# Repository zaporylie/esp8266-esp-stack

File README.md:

# ESP stack

## Goal

Cheap and easy to use (and make it at home) development kit for ESP8266 based projects.

## Available boards

* core, compatible with esp-07 esp-12 and esp-12e
* pl2303 - use it together with external FTDI board

## Contribution

## Licence

This project is licenced under GNU General Public Licence, version 2 or later. You can take it from here, use in free or commercial projects. However, you must distribute it under the GPL version 2 or later, so those you sell it to must be allowed to modify and redistribute it as well.

## Credits

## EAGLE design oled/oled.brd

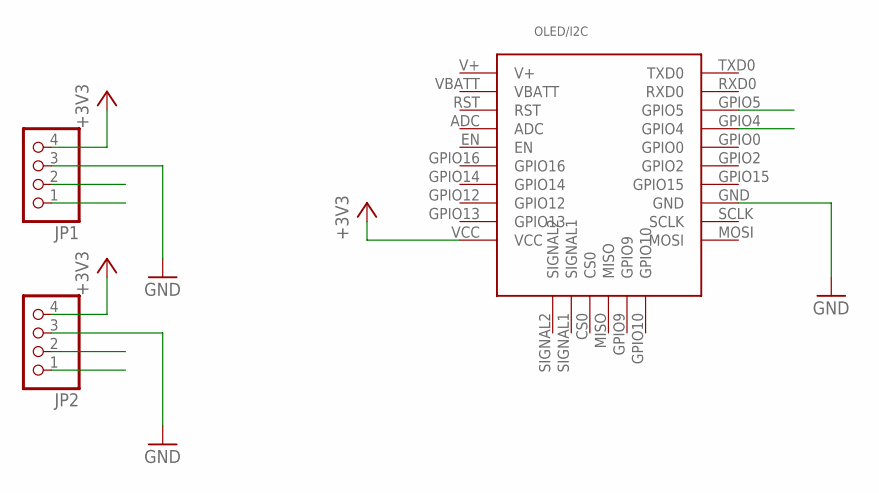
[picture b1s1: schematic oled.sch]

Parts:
JP1, JP2: PINHD-1X4; 1X04
OLED/I2C: ESP-BOARD

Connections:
+3V3: JP1.4, JP2.4, OLED/I2C.VCC
GND: JP1.3, JP2.3, OLED/I2C.GND
SCL: JP1.2, JP2.2, OLED/I2C.GPIO5
SDA: JP1.1, JP2.1, OLED/I2C.GPIO4
V+: OLED/I2C.V+
VBATT: OLED/I2C.VBATT

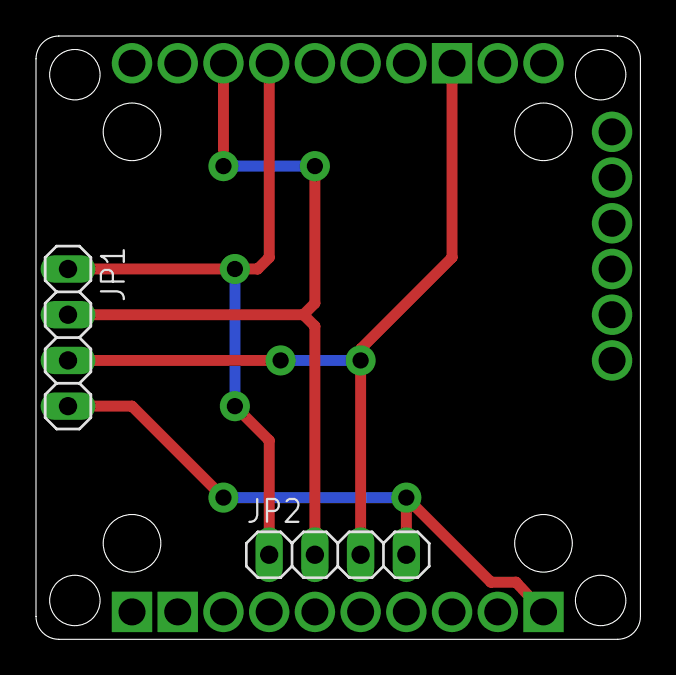
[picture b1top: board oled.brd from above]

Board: 2 copper layers, 33.6 x 33.5 mm, 3 parts (0 on the bottom side), 4 nets.

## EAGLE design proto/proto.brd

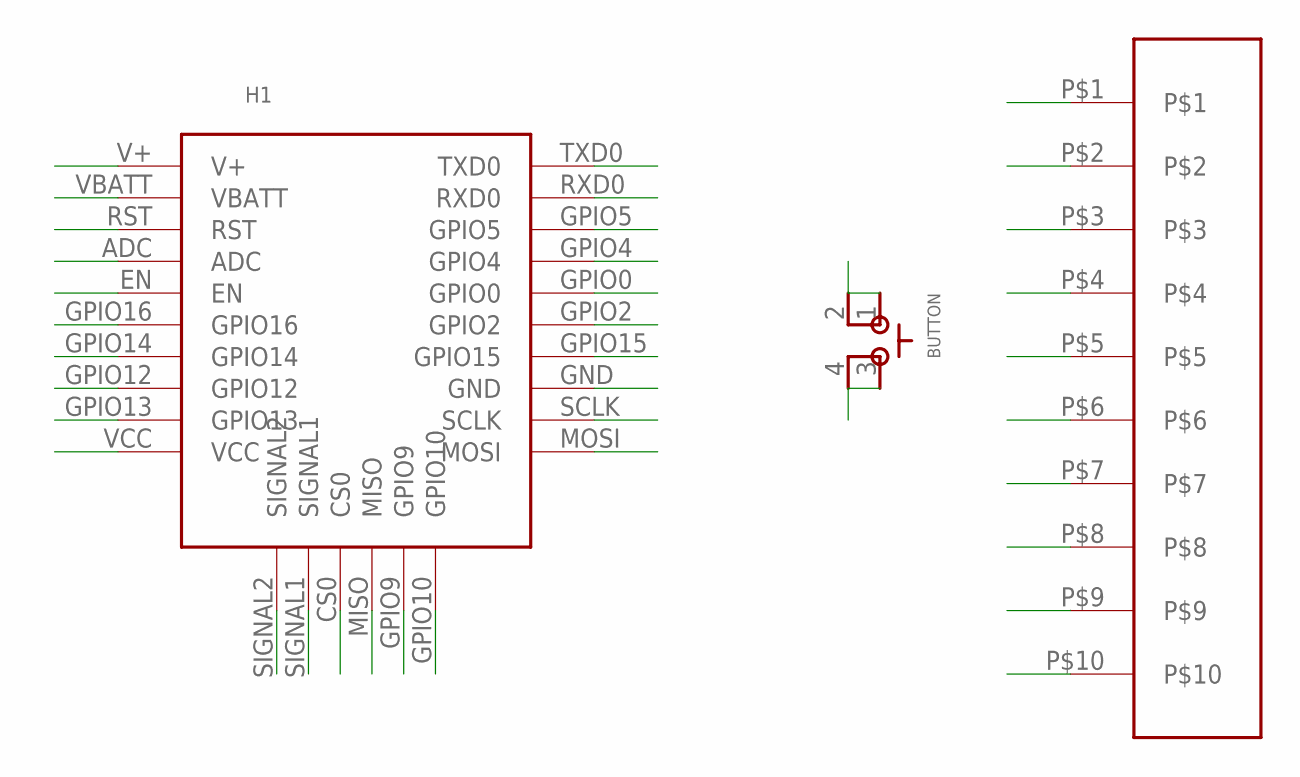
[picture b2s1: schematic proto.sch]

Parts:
BUTTON: SKSCLDE010
H1: ESP-BOARD
U$1: 1X10-EDGE

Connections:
ADC: H1.ADC
CS0: H1.CS0
EN: H1.EN
GND: H1.GND
GPIO0: H1.GPIO0
GPIO2: H1.GPIO2
GPIO4: H1.GPIO4
GPIO5: H1.GPIO5
GPIO9: H1.GPIO9
GPIO10: H1.GPIO10
GPIO12: H1.GPIO12
GPIO13: H1.GPIO13
GPIO14: H1.GPIO14
GPIO15: H1.GPIO15
GPIO16: H1.GPIO16
MISO: H1.MISO
MOSI: H1.MOSI
P0: U$1.P$10
P1: U$1.P$9
P2: U$1.P$8
P3: U$1.P$7
P4: U$1.P$6
P5: U$1.P$5
P6: U$1.P$4
P7: U$1.P$3
P8: U$1.P$2
P9: U$1.P$1
RST: H1.RST
RXD0: H1.RXD0
SCLK: H1.SCLK
SIGNAL1: H1.SIGNAL1
SIGNAL2: H1.SIGNAL2
SW1: BUTTON.3 (4), BUTTON.4 (3)
SW2: BUTTON.1, BUTTON.2
TXD0: H1.TXD0
V+: H1.V+
VBATT: H1.VBATT
VCC: H1.VCC

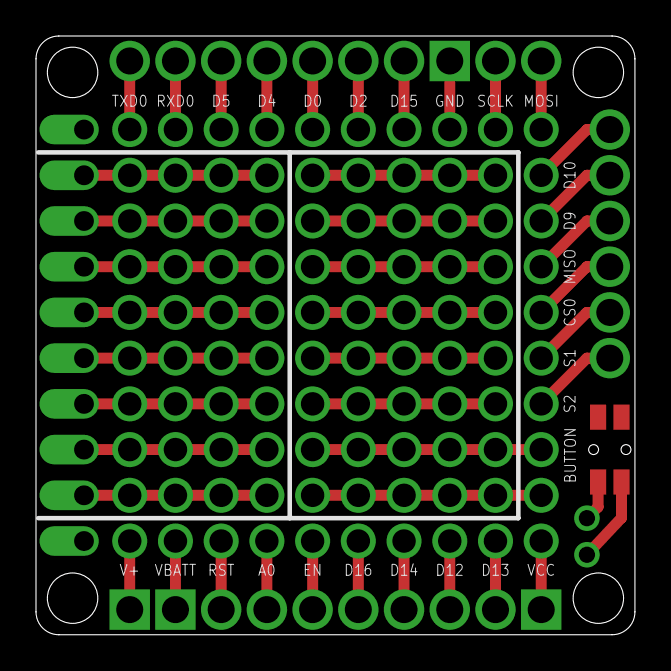
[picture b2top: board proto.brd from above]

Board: 2 copper layers, 33.3 x 33.3 mm, 3 parts (0 on the bottom side), 2 nets.

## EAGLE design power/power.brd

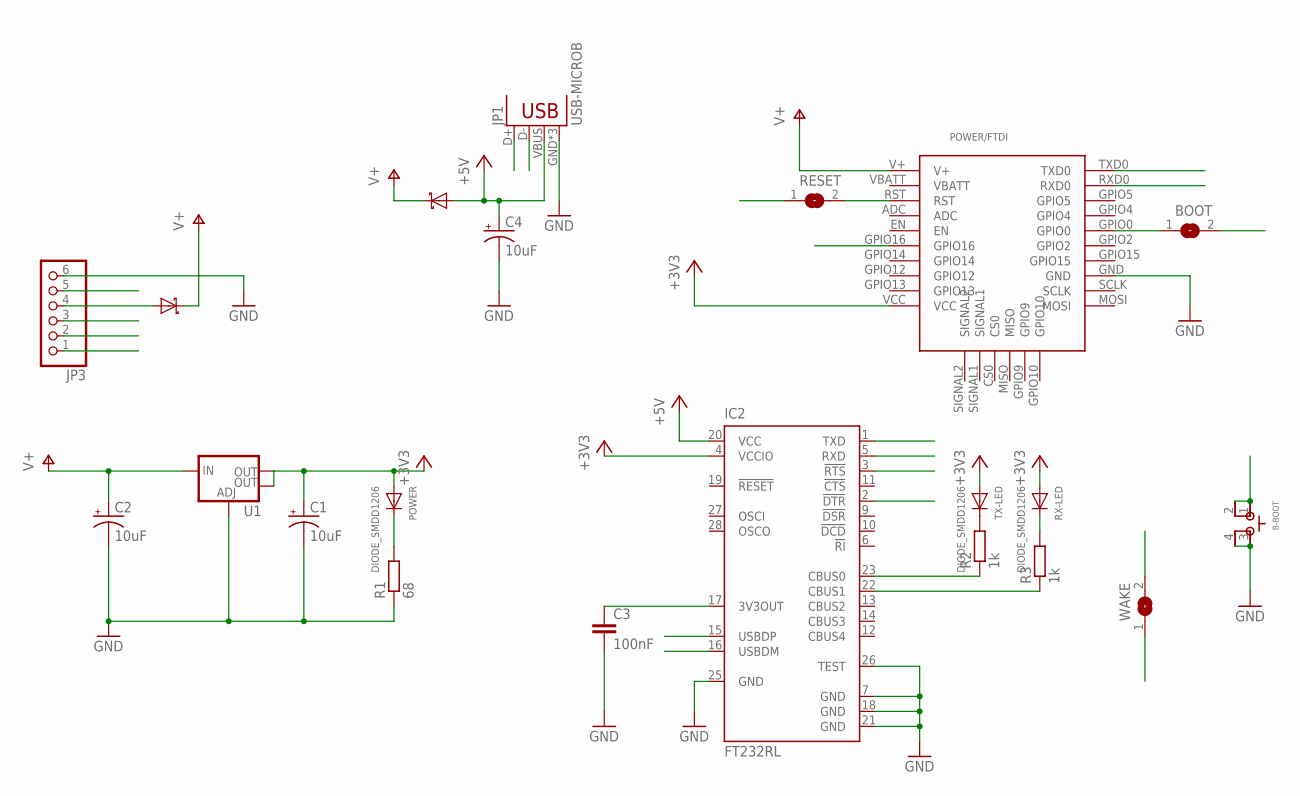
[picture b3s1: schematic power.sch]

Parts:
B-BOOT: SKSCLDE010
BOOT: SJ
C1, C2, C4: 10uF; EIA3216
C3: 100nF; C0805
D1, D2: MBR120; SOD123
IC2: FT232RL; SSOP28
JP1: USB-MICROB
JP3: PINHD-1X6; 1X06
POWER: DIODE_SMDD1206; D1206
POWER/FTDI: ESP-BOARD
R1: 68; R1206
R2, R3: 1k; R1206
RESET: SJ
RX-LED: DIODE_SMDD1206; D1206
TX-LED: DIODE_SMDD1206; D1206
U1: V_REG_LM1117SOT223; SOT223
WAKE: SJ

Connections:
+3V3: C1.A (+), IC2.4 (VCCIO), POWER.A, POWER/FTDI.VCC, RX-LED.A, TX-LED.A, U1.2 (OUT), U1.4 (OUT)
+5V: C4.A (+), D1.A, IC2.20 (VCC), JP1.VBUS
D+: IC2.15 (USBDP), JP1.D+
D-: IC2.16 (USBDM), JP1.D-
DTR: B-BOOT.1, B-BOOT.2, BOOT.2, IC2.2 (!DTR), JP3.5
GND: B-BOOT.3 (4), B-BOOT.4 (3), C1.C (-), C2.C (-), C3.2, C4.C (-), IC2.7 (GND), IC2.18 (GND), IC2.21 (GND), IC2.25 (GND), IC2.26 (TEST), JP1.GND, JP1.MT1 (GND), JP1.MT2 (GND), JP3.6, POWER/FTDI.GND, R1.1, U1.1 (ADJ)
GPIO0: BOOT.1, POWER/FTDI.GPIO0
GPIO16: POWER/FTDI.GPIO16, WAKE.1
unnamed: POWER.K, R1.2
unnamed: IC2.22 (CBUS1), R3.1
unnamed: R2.2, TX-LED.K
unnamed: IC2.23 (CBUS0), R2.1
unnamed: D2.A, JP3.4
unnamed: R3.2, RX-LED.K
unnamed: C3.1, IC2.17 (3V3OUT)
RST: POWER/FTDI.RST, RESET.2, WAKE.2
RTS: IC2.3 (!RTS), JP3.1, RESET.1
RXD: IC2.5 (RXD), JP3.2, POWER/FTDI.TXD0
TXD: IC2.1 (TXD), JP3.3, POWER/FTDI.RXD0
V+: C2.A (+), D1.C, D2.C, POWER/FTDI.V+, U1.3 (IN)
VBATT: POWER/FTDI.VBATT

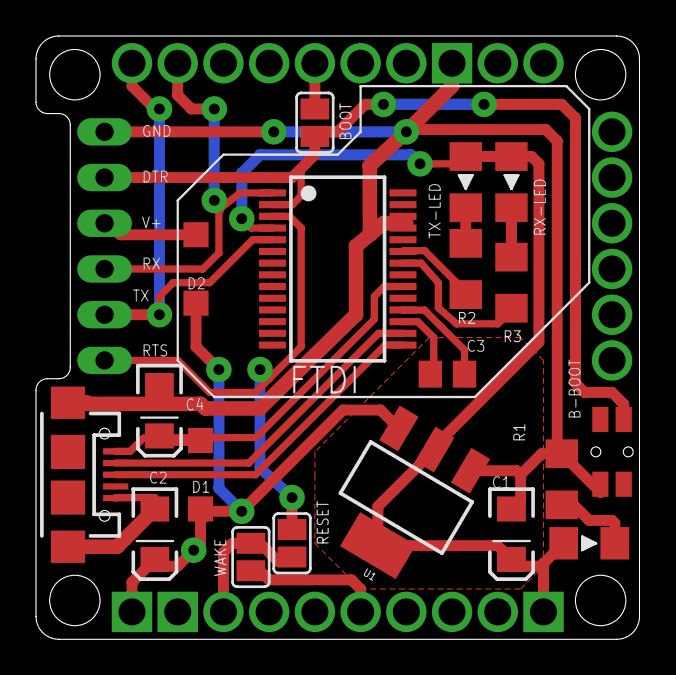
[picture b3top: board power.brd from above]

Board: 2 copper layers, 33.5 x 33.5 mm, 21 parts (0 on the bottom side), 20 nets.

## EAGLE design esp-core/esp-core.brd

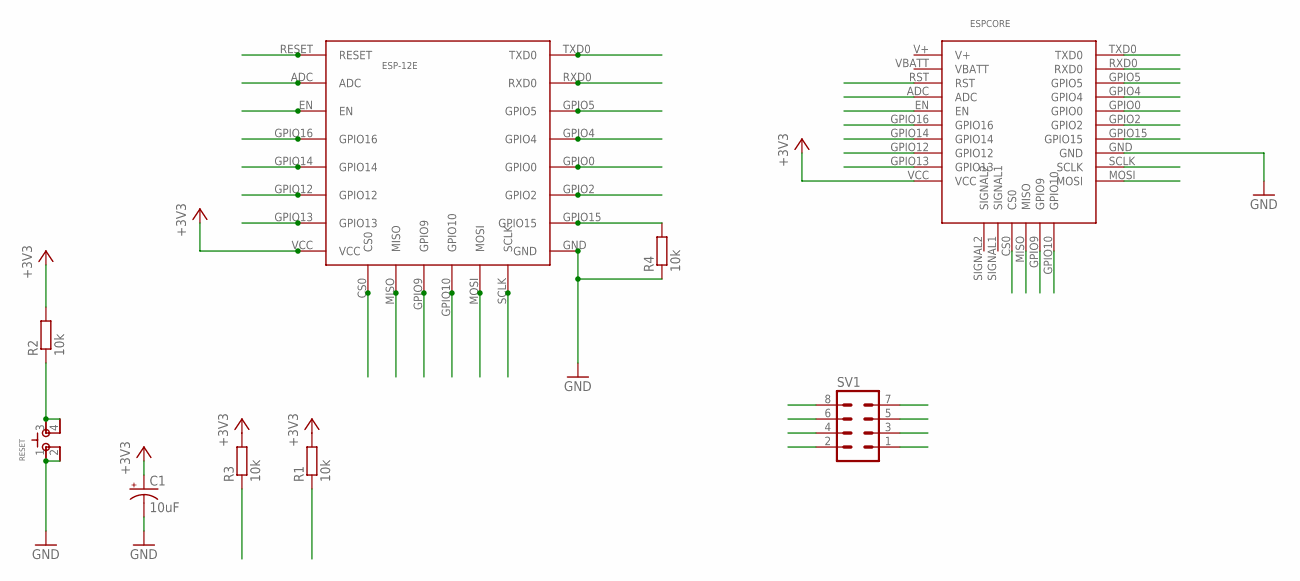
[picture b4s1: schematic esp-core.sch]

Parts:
C1: 10uF; EIA3216
ESP-12E: ESP-12E
ESPCORE: ESP-BOARD
R1, R2, R3, R4: 10k; R1206
RESET: SKSCLDE010
SV1: MA04-2

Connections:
+3V3: C1.A (+), ESP-12E.VCC, ESPCORE.VCC, R1.2, R2.2, R3.2, SV1.7
ADC: ESP-12E.ADC, ESPCORE.ADC
CS0: ESP-12E.CS0, ESPCORE.CS0
EN: ESP-12E.EN, ESPCORE.EN, R1.1, SV1.3
GND: C1.C (-), ESP-12E.GND, ESPCORE.GND, R4.1, RESET.1, RESET.2, SV1.2
GPIO0: ESP-12E.GPIO0, ESPCORE.GPIO0, R3.1, SV1.6
GPIO2: ESP-12E.GPIO2, ESPCORE.GPIO2, SV1.4
GPIO4: ESP-12E.GPIO4, ESPCORE.GPIO4
GPIO5: ESP-12E.GPIO5, ESPCORE.GPIO5
GPIO9: ESP-12E.GPIO9, ESPCORE.GPIO9
GPIO10: ESP-12E.GPIO10, ESPCORE.GPIO10
GPIO12: ESP-12E.GPIO12, ESPCORE.GPIO12
GPIO13: ESP-12E.GPIO13, ESPCORE.GPIO13
GPIO14: ESP-12E.GPIO14, ESPCORE.GPIO14
GPIO15: ESP-12E.GPIO15, ESPCORE.GPIO15, R4.2
GPIO16: ESP-12E.GPIO16, ESPCORE.GPIO16
MISO: ESP-12E.MISO, ESPCORE.MISO
MOSI: ESP-12E.MOSI, ESPCORE.MOSI
RESET: ESP-12E.RESET, ESPCORE.RST, R2.1, RESET.3 (4), RESET.4 (3), SV1.5
RXD0: ESP-12E.RXD0, ESPCORE.RXD0, SV1.8
SCLK: ESP-12E.SCLK, ESPCORE.SCLK
TXD0: ESP-12E.TXD0, ESPCORE.TXD0, SV1.1
V+: ESPCORE.V+
VBATT: ESPCORE.VBATT

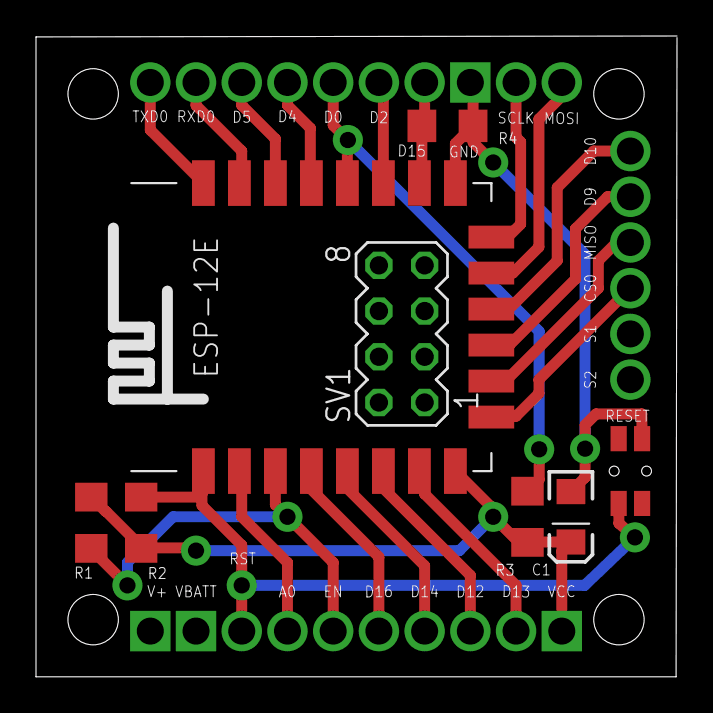
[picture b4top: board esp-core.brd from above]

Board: 2 copper layers, 35.6 x 35.6 mm, 10 parts (0 on the bottom side), 22 nets.

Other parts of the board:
U$1: OSHW2

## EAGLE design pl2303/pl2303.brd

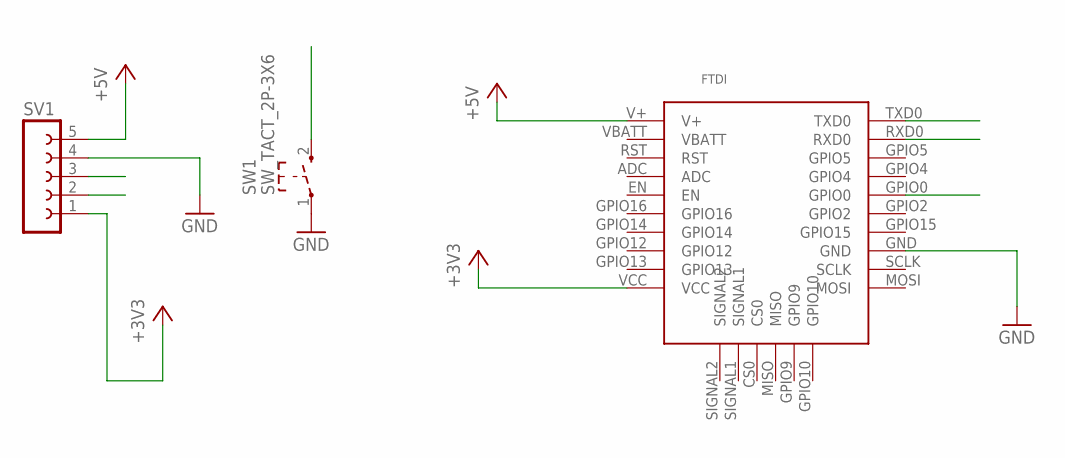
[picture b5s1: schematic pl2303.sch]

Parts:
FTDI: ESP-BOARD
SV1: FE05-1
SW1: SW_TACT_2P-3X6; SW_TACT_3X6

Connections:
+3V3: FTDI.VCC, SV1.1
+5V: FTDI.V+, SV1.5
GND: FTDI.GND, SV1.4, SW1.1
GPIO0: FTDI.GPIO0, SW1.2 (3)
RXD0: FTDI.RXD0, SV1.2
TXD0: FTDI.TXD0, SV1.3
VBATT: FTDI.VBATT

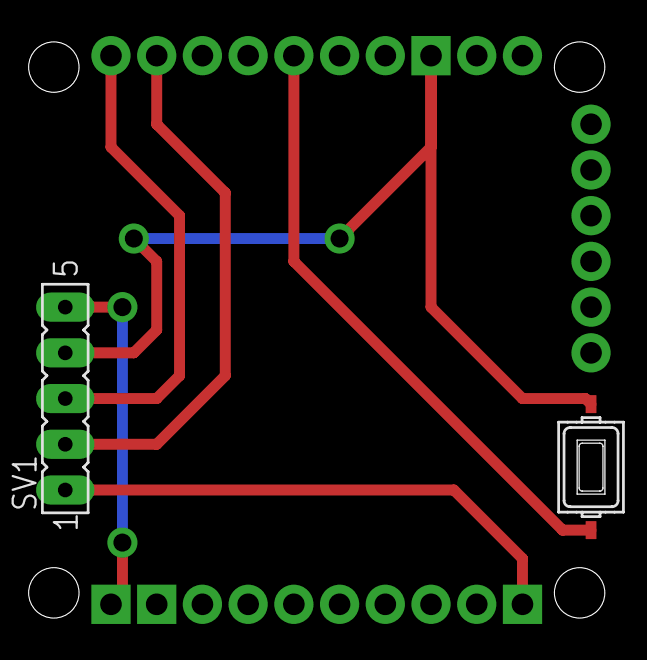
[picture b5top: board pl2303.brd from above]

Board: 2 copper layers, 3 parts (0 on the bottom side), 6 nets.

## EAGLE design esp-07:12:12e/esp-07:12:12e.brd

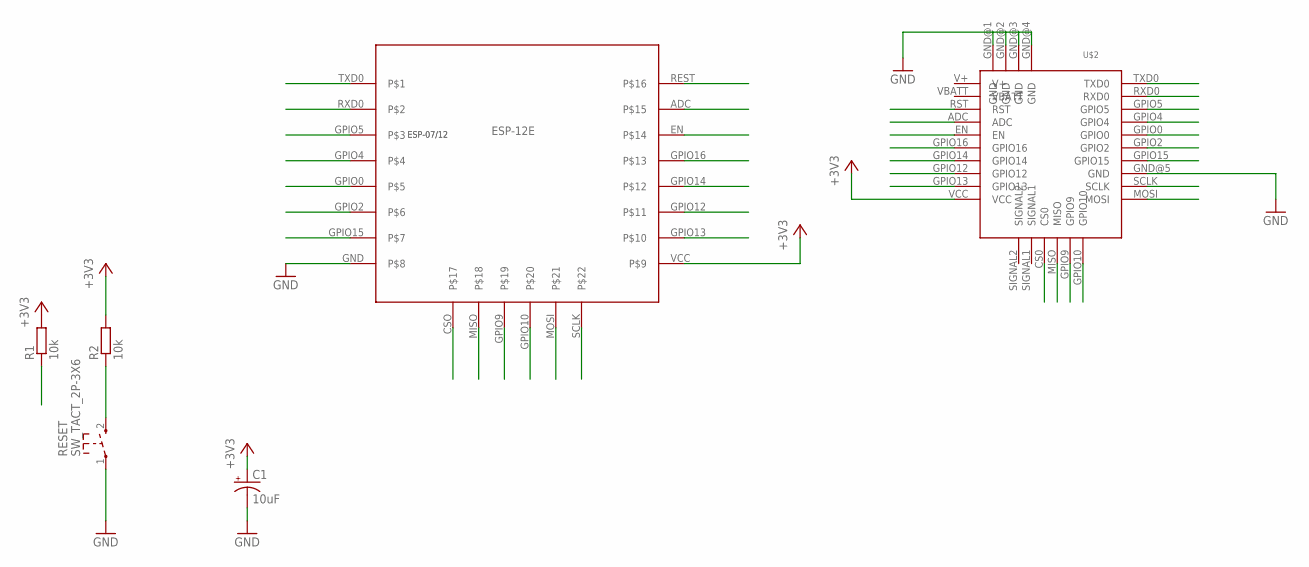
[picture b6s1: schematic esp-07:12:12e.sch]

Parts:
C1: 10uF; EIA3216
R1, R2: 10k; R1206
RESET: SW_TACT_2P-3X6; SW_TACT_3X6
U$1: ESP-07/12_ESP-12E; ESP-07/12
U$2: ESP-BOARD

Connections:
+3V3: C1.A (+), R1.2, R2.2, U$1.VCC, U$2.VCC
ADC: U$1.ADC, U$2.ADC
CS0: U$1.CSO, U$2.CS0
EN: R1.1, U$1.EN, U$2.EN
GND: C1.C (-), RESET.1, U$1.GND, U$2.GND@1 (GND), U$2.GND@2 (GND), U$2.GND@3 (GND), U$2.GND@4 (GND), U$2.GND@5 (GND)
GPIO0: U$1.GPIO0, U$2.GPIO0
GPIO2: U$1.GPIO2, U$2.GPIO2
GPIO4: U$1.GPIO4, U$2.GPIO4
GPIO5: U$1.GPIO5, U$2.GPIO5
GPIO9: U$1.GPIO9, U$2.GPIO9
GPIO10: U$1.GPIO10, U$2.GPIO10
GPIO12: U$1.GPIO12, U$2.GPIO12
GPIO13: U$1.GPIO13, U$2.GPIO13
GPIO14: U$1.GPIO14, U$2.GPIO14
GPIO15: U$1.GPIO15, U$2.GPIO15
GPIO16: U$1.GPIO16, U$2.GPIO16
MISO: U$1.MISO, U$2.MISO
MOSI: U$1.MOSI, U$2.MOSI
RESET: R2.1, RESET.2 (3), U$1.REST, U$2.RST
RXD0: U$1.RXD0, U$2.RXD0
SCLK: U$1.SCLK, U$2.SCLK
TXD0: U$1.TXD0, U$2.TXD0
V+: U$2.V+
VBATT: U$2.VBATT

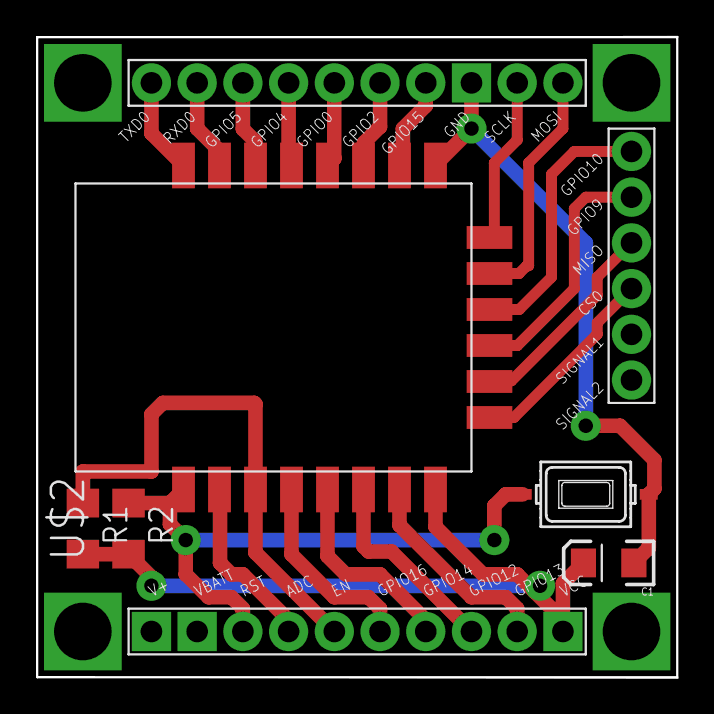
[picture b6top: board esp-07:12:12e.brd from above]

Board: 2 copper layers, 35.6 x 35.6 mm, 6 parts (0 on the bottom side), 22 nets.

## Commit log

2015-06-06 Core board, compatibile with esp-07, esp-12, esp-12e
2015-06-06 Added capacitor for power stability
2015-06-07 Add power board - micro USB, LDO 3.3V, capacitors and status LED + spare input header
2015-06-08 Fix paths under ESP board - shouldn't overlap with module pads
2015-06-14 New board size - 1.4 inches; reduced number of signal pins to only two; mounting holes
2015-06-14 FTDI board update - new board size and mounting holes
2015-06-14 Small clearance improvements, bigger header pads and mounting holes
2015-06-16 Add ESP library
2015-06-16 Modify ESP library - add ESP module component
2015-06-16 New version of esp-core board
2015-06-17 New board schema applied to ftdi module
2015-06-19 Add pull-up and down resistors to 'special' pins - GPIO0 and GPIO15
2015-06-19 OLED/i2c board
2015-06-20 Removed unused device from library, change drill size.
2015-06-21 Remove pins description from library. Start new package for ESP-12e
2015-06-21 Fix small DRC issues with esp-core board
2015-06-22 Add new part to library - tact switch
2015-06-22 Fix button on board
2015-06-23 Submodule with open hardware icons
2015-06-23 Add openhardware icon to library and to core board
2015-07-01 esp-core v0.1
2015-07-01 Useful libraries
2015-07-01 Power/FTDI board
2015-07-02 Power board (USB, external power, FT232RL section
2015-07-02 Removed pl2303 since power board will cover this part
2015-07-02 Small library fixes
2015-07-16 Changes to library
2015-07-16 Small improvements to usb board
2015-07-16 proto board
2015-07-16 core board fixes
2015-07-17 Unify all boards, buttons in the same place, board dimension reduced to 1.32inch
2015-07-22 Improve oled board

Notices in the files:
parts and their libraries:
SparkFun-Capacitors: Licensing: Creative Commons ShareAlike 4.0 International - https://creativecommons.org/licenses/by-sa/4.0
